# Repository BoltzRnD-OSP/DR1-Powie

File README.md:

# DR1-Powie ☺  
UAVCAN-Based Power Module for DR1 Series Flight Controllers

# Specifications:

Voltage: 3S - 12S  
Current Rating: 10A - 90A  
Embedded 5V 2A Buck to power the Flight Controller  
Battery Gauge LEDs (Will be functional in the near future)  

# License
This project is licensed under the Attribution-ShareAlike 4.0 International License.

You are free to commercially utilize the project and its derivatives. Please be generous and provide attribution! :)

THANKS!

Note: The Boltz R&D wordmark and lightning logo are trademarks of Boltz R&D. Any use other than for attribution of "this" project is strictly prohibited.

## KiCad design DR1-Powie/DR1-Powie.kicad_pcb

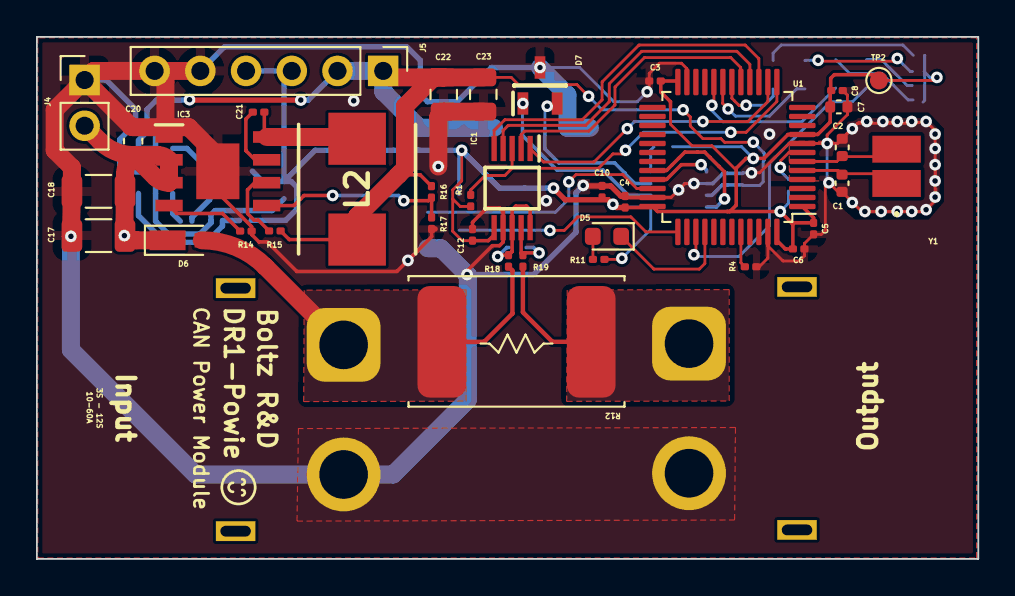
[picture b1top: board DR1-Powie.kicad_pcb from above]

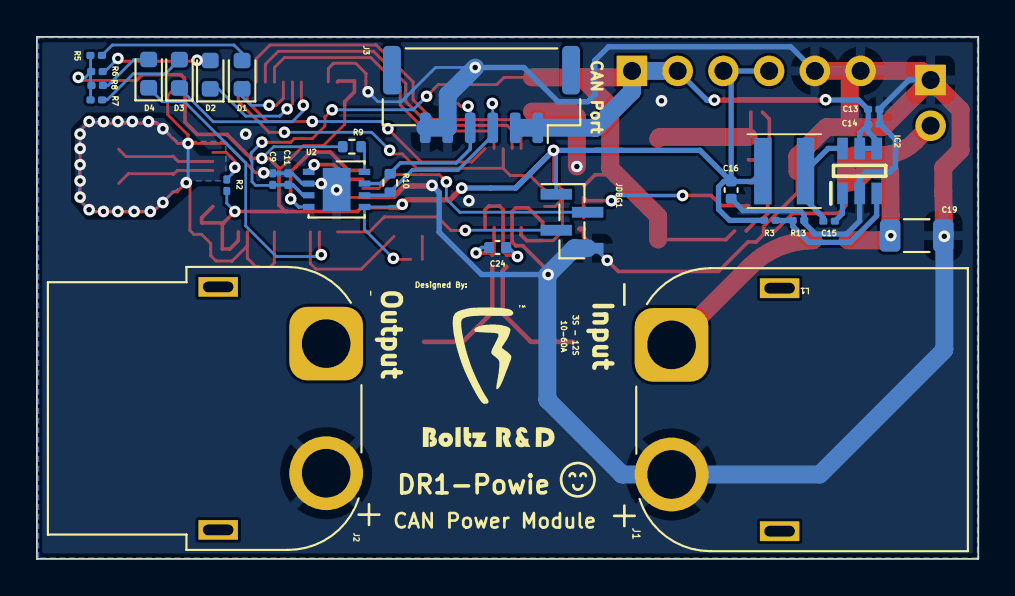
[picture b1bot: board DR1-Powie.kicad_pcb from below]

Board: 2 copper layers, 52.3 x 29.0 mm, 65 parts (28 on the bottom side), 42 nets.

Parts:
C1, C2: 8pF 1%; C_0402_1005Metric
C3, C4, C5, C6, C12, C14, C15, C21: 100nf; C_0201_0603Metric
C7: 10nf; C_0402_1005Metric
C8: 1uF; C_0201_0603Metric
C9, C11: 100nF; C_0201_0603Metric
C10, C13: 4.7uF; C_0201_0603Metric
C16: 10uF; C_0402_1005Metric
C17, C18, C19: 4.7uF 63V; C_1206_3216Metric
C20: 100nf 100V; C_0603_1608Metric
C22, C23: 47uF; C_0805_2012Metric
C24: 100nf 100V; C_0402_1005Metric
D1, D2, D3, D4, D5: LED; LED_0603_1608Metric
D6: V2PM10HM3/H; D_MicroSMP_AK
D7: CDSOT23-T24CAN; SOT95P230X117-3N
IC1: INA239AIDGSR; SOP50P490X110-10N
IC2: LMR54406DBVR; SOT95P280X145-6N
IC3: LMR38020SDDAR; SOIC127P600X170-9N
J1: Conn_01x02; AMASS_XT60PW-M_1x02_P7.20mm_Horizontal
J2: Conn_01x02; AMASS_XT60PW-F_1x02_P7.20mm_Horizontal
J3: Conn_01x06; JST_GH_SM06B-GHS-TB_1x06-1MP_P1.25mm_Horizontal
J4: Conn_01x02; PinHeader_1x02_P2.54mm_Vertical
J5: Conn_01x06; PinHeader_1x06_P2.54mm_Vertical
JDBG1: Conn_01x04; PinHeader_1x04_P1.00mm_Vertical_SMD_Pin1Left
L1: 5.6uH 0.6A(Min); Inductor
L2: 15uH 2A(Min); INDPM7265X400N
R1, R2, R4: 10K; R_0201_0603Metric
R3: 69.8K; C_0201_0603Metric
R5, R6, R7, R8, R11: 220E; R_0201_0603Metric
R9: 10K; R_0402_1005Metric
R10: 120E; R_0402_1005Metric
R12: 0.5MOhm 9W; BVS-M-R0005-1.0
R13: 22.1K; C_0201_0603Metric
R14: 64.9K; C_0201_0603Metric
R15: 100K; R_0201_0603Metric
R16: 40.2K 1%; C_0201_0603Metric
R17: 10K 1%; C_0201_0603Metric
R18, R19: 220E 0.1%; R_0201_0603Metric
TP2: TestPoint; TestPoint_Pad_D1.0mm
U1: STM32L431CBTx; LQFP-48_7x7mm_P0.5mm
U2: TJA1051TK-3; DFN-8-1EP_3x3mm_P0.65mm_EP1.55x2.4mm
Y1: NX3225GD-8MHZ-EXS00A-CG04874; NX3225GD8MHZSTDCRA3

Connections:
+5V: C9.1, C11.1, C13.1, C14.1, C22.1, C23.1, IC2.4 (EN), IC2.5 (VIN), J3.1, J3.2, J5.1, J5.2, L2.2, R15.1, R16.1, U2.3 (VCC)
+BATT: C17.1, C18.1, C19.1, C20.1, D6.1 (K), IC3.2 (EN), IC3.3 (VIN), J4.2
BOOT0: R4.1, U1.44 (PH3)
CAN1_RX: U1.32 (PA11), U2.4 (RXD)
CAN1_TX: U1.33 (PA12), U2.1 (TXD)
CAN_H_1: D7.2 (K2), J3.4, R10.1, U2.7 (CANH)
CAN_L_1: D7.1 (K1), J3.3, R10.2, U2.6 (CANL)
CSENSE1: C24.1, IC1.8 (VBUS), IC1.10 (IN+), R18.1
CSENSE2: C24.2, IC1.9 (IN-), R19.1
CSNSR_ALERT: IC1.3 (ALERT), R1.1, U1.13 (PA3)
CSNSR_CS: IC1.1 (CS), U1.14 (PA4)
CSNSR_MISO: IC1.4 (MISO), U1.16 (PA6)
CSNSR_MOSI: IC1.2 (MOSI), U1.17 (PA7)
CSNSR_SCLK: IC1.5 (SCLK), U1.15 (PA5)
FMU_SWCLK: JDBG1.3, U1.37 (PA14)
FMU_SWDIO: JDBG1.2, U1.34 (PA13)
GAUGE_LED1: D1.1 (K), U1.18 (PB0)
GAUGE_LED2: D2.1 (K), U1.19 (PB1)
GAUGE_LED3: D3.1 (K), U1.20 (PB2)
GAUGE_LED4: D4.1 (K), U1.39 (PB3)
GND: C1.2, C2.2, C3.2, C4.2, C5.2, C6.2, C7.2, C8.2, C9.2, C10.2, C11.2, C12.2, C13.2, C14.2, C16.2, C17.2, C18.2, C19.2, C20.2, C22.2, C23.2, D7.3 (K3), IC1.7 (GND), IC2.2 (GND), IC3.1 (GND), IC3.9 (EP), J1.2, J2.2, J3.5, J3.6, J4.1, J5.5, J5.6, JDBG1.4, R4.2, R13.2, R14.2, R17.2, U1.8 (VSSA), U1.23 (VSS), U1.35 (VSS), U1.47 (VSS), U2.2 (GND), U2.9 (GND)
MCU_OSCIN: C1.1, U1.5 (PH0), Y1.1
MCU_OSCOUT: C2.1, U1.6 (PH1), Y1.2
unnamed: D1.2 (A), R5.1
unnamed: D2.2 (A), R6.1
unnamed: D3.2 (A), R7.1
unnamed: D4.2 (A), R8.1
unnamed: D5.2 (A), R11.1
unnamed: C15.2, IC2.1 (CB)
unnamed: IC2.3 (FB), R3.2, R13.1
unnamed: C15.1, IC2.6 (SW), L1.1
unnamed: C21.1, IC3.7 (BOOT)
unnamed: IC3.5 (FB), R16.2, R17.1
unnamed: IC3.6 (PG), R15.2
unnamed: IC3.4 (RT/SYNC), R14.1
unnamed: C21.2, IC3.8 (SW), L2.1
unnamed: R2.1, U1.7 (NRST)
unnamed: R9.1, U2.8 (S)
PSU: D6.2 (A), J1.1, R12.2, R18.2
PSU2: J2.1, R12.1, R19.2
UI_LED: D5.1 (K), U1.40 (PB4)
VDD: C3.1, C4.1, C5.1, C6.1, C7.1, C8.1, C10.1, C12.1, C16.1, IC1.6 (VS), J5.3, J5.4, JDBG1.1, L1.2, R1.2, R2.2, R3.1, R5.2, R6.2, R7.2, R8.2, R9.2, R11.2, TP2.1, U1.1 (VBAT), U1.9 (VDDA), U1.24 (VDD), U1.36 (VDD), U1.48 (VDD), U2.5 (VIO)

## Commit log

2023-09-10 Added Files
